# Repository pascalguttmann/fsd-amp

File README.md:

# fsd-amp

Linear Audio Amplifier as demonstration for workshop at Freie Schule Dreisamtal.
PCB is used as a demonstrator for soldering excercises and fundamentals of circuit design.

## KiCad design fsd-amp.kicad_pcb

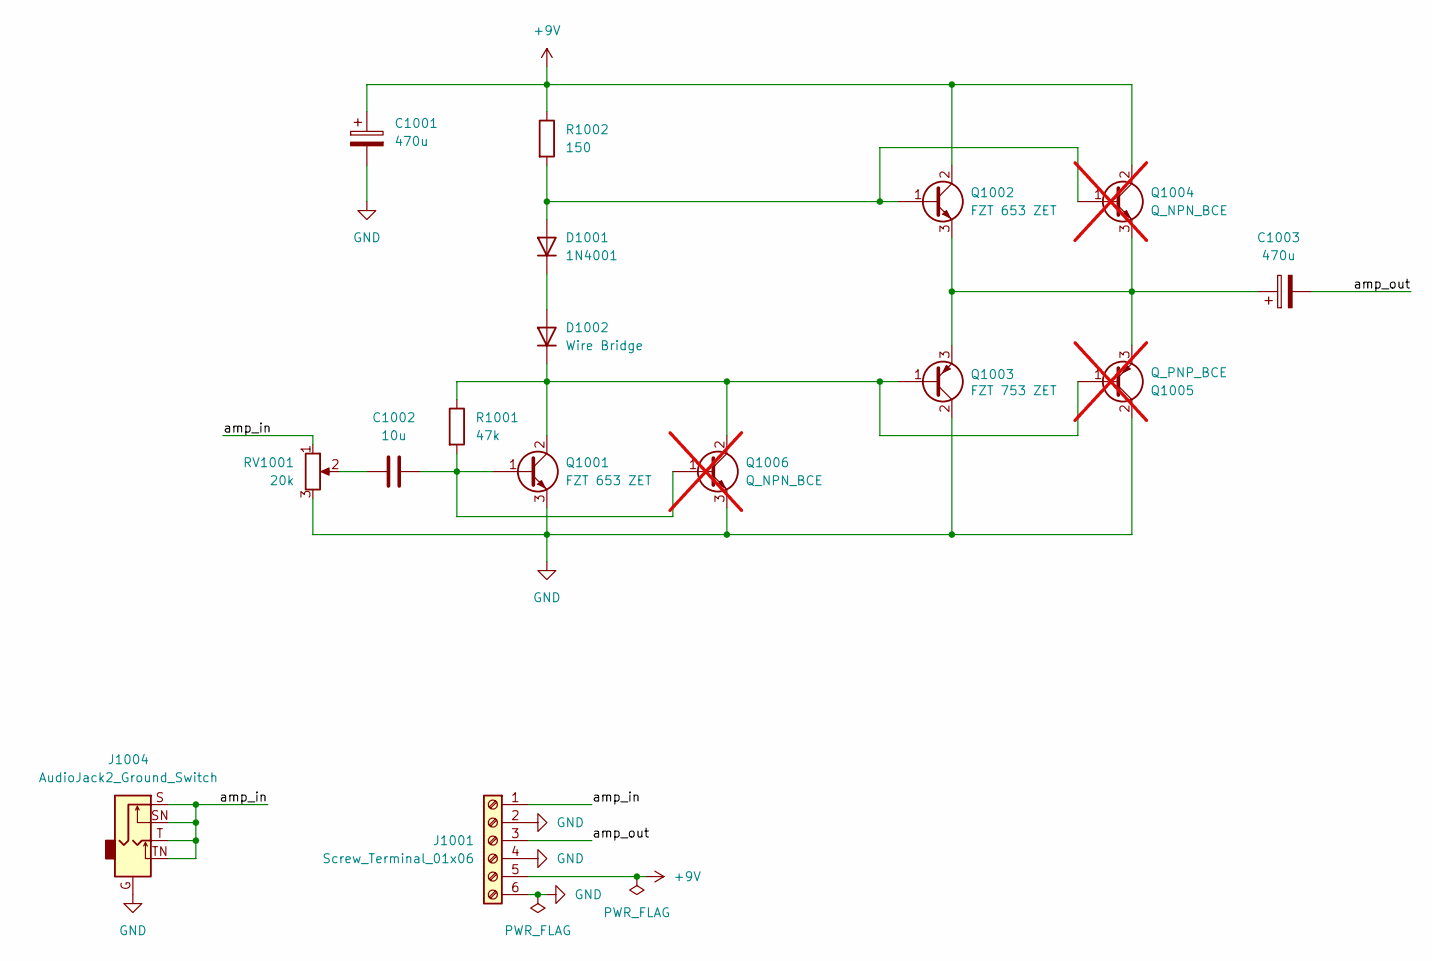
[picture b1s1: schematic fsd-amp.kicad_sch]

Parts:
C1001, C1003: 470u; CP_Radial_D10.0mm_P5.00mm
C1002: 10u; C_Rect_L7.2mm_W11.0mm_P5.00mm_FKS2_FKP2_MKS2_MKP2
D1001: 1N4001; D_DO-41_SOD81_P10.16mm_Horizontal
D1002: Wire Bridge; D_DO-41_SOD81_P10.16mm_Horizontal
J1001: Screw_Terminal_01x06; TerminalBlock_MetzConnect_Type101_RT01606HBWC_1x06_P5.08mm_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
J1004: AudioJack2_Ground_Switch; Jack_3.5mm_Ledino_KB3SPRS_Horizontal
Q1001, Q1002: FZT 653 ZET; SOT-223-3_TabPin2
Q1003: FZT 753 ZET; SOT-223-3_TabPin2
Q1004, Q1006: Q_NPN_BCE; TO-92_Inline_Wide_NOcourtyard; not fitted
Q1005: Q_PNP_BCE; TO-92_Inline_Wide_NOcourtyard; not fitted
R1001: 47k; R_Axial_DIN0207_L6.3mm_D2.5mm_P10.16mm_Horizontal
R1002: 150; R_Axial_DIN0207_L6.3mm_D2.5mm_P10.16mm_Horizontal
RV1001: 20k; Potentiometer_Bourns_3296W_Vertical

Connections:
+9V: C1001.1, J1001.5, Q1002.2 (C), Q1004.2 (C), R1002.1
/amp_in: J1001.1, J1004.S, J1004.SN, J1004.T, J1004.TN, RV1001.1
/amp_out: C1003.2, J1001.3
GND: C1001.2, J1001.2, J1001.4, J1001.6, J1004.G, Q1001.3 (E), Q1003.2 (C), Q1005.2 (C), Q1006.3 (E), RV1001.3
unnamed: C1002.1, RV1001.2
unnamed: D1001.2 (A), Q1002.1 (B), Q1004.1 (B), R1002.2
unnamed: D1001.1 (K), D1002.2 (A)
unnamed: D1002.1 (K), Q1001.2 (C), Q1003.1 (B), Q1005.1 (B), Q1006.2 (C), R1001.1
unnamed: C1002.2, Q1001.1 (B), Q1006.1 (B), R1001.2
unnamed: C1003.1, Q1002.3 (E), Q1003.3 (E), Q1004.3 (E), Q1005.3 (E)

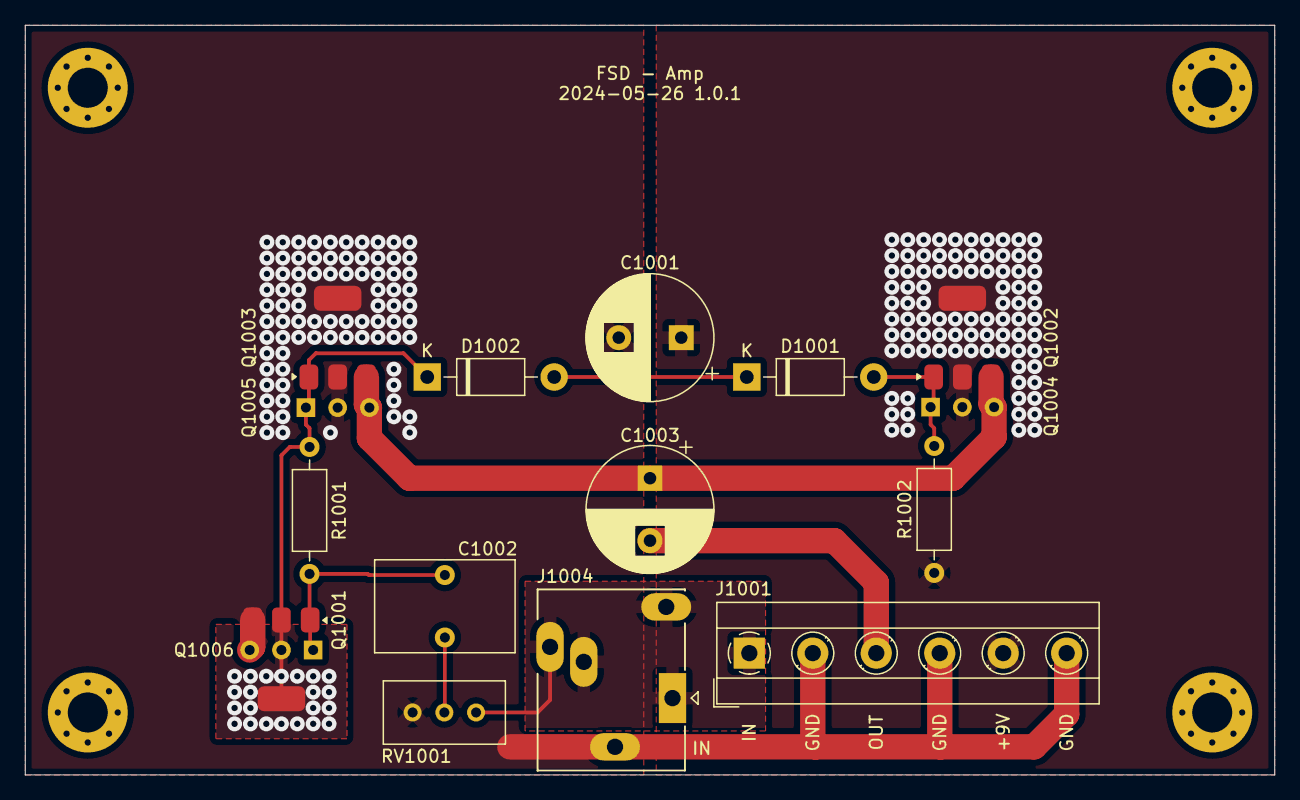
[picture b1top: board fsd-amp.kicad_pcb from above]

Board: 2 copper layers, 100.0 x 60.0 mm, 16 parts (0 on the bottom side), 10 nets.

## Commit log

2024-05-24 enhance gitignore
2024-05-24 add KiCad project
2024-05-24 add schematic labels and settings
2024-05-24 add schematic
2024-05-24 add parts from reichelt
2024-05-24 add poti for volume adjustment
2024-05-24 fix ERC pwr_flag error
2024-05-24 add footprints
2024-05-24 export footprints and symbols to project libraries
2024-05-24 add pcb DRU, Standard Sizes and Netclasses
2024-05-24 adjust silk screen default settings
2024-05-24 define edge cuts board outline
2024-05-24 coarse placement of footprints
2024-05-26 fix placement of power bjt
2024-05-26 add routing
2024-05-26 widen thermal relief spokes
2024-05-26 add netclass colorization
2024-05-26 add fill zone bottom side
2024-05-26 add thermal relief for transistors
2024-05-26 fix drc errors
2024-05-26 fix drc warnings, enhace silkscreen
    - fix drc warnings (silk screen related)
    - move mounting holes to 'fp' library
    - enhance silkscreen placement
    - remove outline silkscreen from SOT-223 footprint
    - remove silkscreen out of board from audion jack
2024-05-26 add backup THT transistor footprint
2024-05-26 add connection labels on silkT
2024-05-26 add title at f.silk
2024-05-26 add fp library with TO-92 footprints
2024-05-26 add variable substitution for date and revision
2024-05-26 add preview image v1.0.0
2024-05-26 fix small trace in plane, creating spoke at pads
2024-05-27 add order 240527
    - bom export
    - excel order overview
    - ungitignore bom export
2024-06-08 pcb auto rotate of components 360 deg
2024-06-08 add ibom config
2024-06-08 add brd 1.0.1 ibom
2024-06-08 adapt ibom config
2024-06-08 remove do not populate parts from ibom
2024-06-08 add schematic version to ibom name
2024-06-08 fix excess quiescent current
    - bias voltage is to high resulting in excess current flow of approx 1A in the complementary emitter follower
    - replace D1002 from diode to wire bridge to reduce the bias voltage
    ´
2024-06-08 bump patch version of schematic
    - add ibom for sch1.0.1
    - add schematic 1.0.1
2024-11-11 Add preview image to README.md
